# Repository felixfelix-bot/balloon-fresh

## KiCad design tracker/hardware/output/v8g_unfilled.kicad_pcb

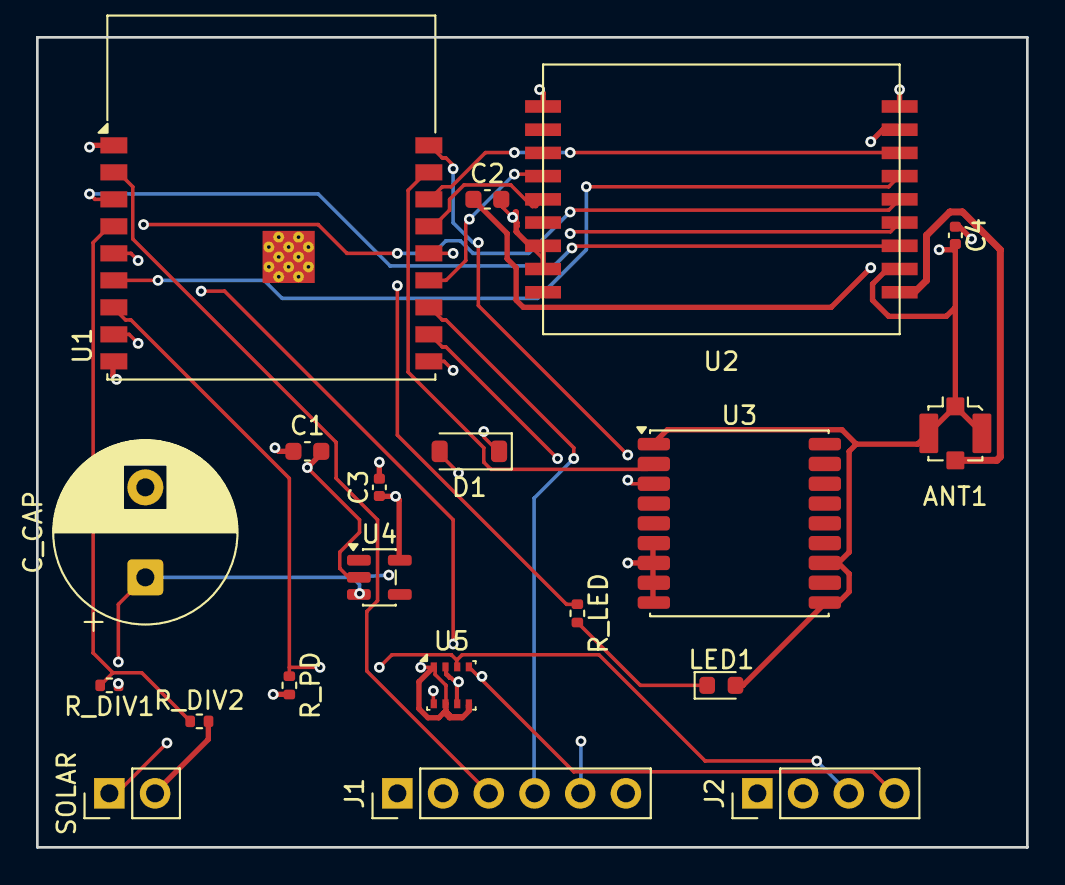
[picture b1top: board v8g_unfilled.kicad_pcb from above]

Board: 4 copper layers, 55.0 x 45.0 mm, 20 parts (0 on the bottom side), 22 nets.

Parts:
ANT1: U.FL; U.FL_Molex_MCRF_73412-0110_Vertical
C1, C2: 10uF; C_0603_1608Metric
C3, C4: 100nF; C_0402_1005Metric
C_CAP: 1F_5.5V; CP_Radial_D10.0mm_P5.00mm
D1: BAT54; D_SOD-123
J1: Prog_Header; PinHeader_1x06_P2.54mm_Vertical
J2: Debug_Header; PinHeader_1x04_P2.54mm_Vertical
LED1: LED_RED; LED_0603_1608Metric
R_DIV1, R_DIV2: 100k; R_0402_1005Metric
R_LED: 330R; R_0402_1005Metric
R_PD: 10k; R_0402_1005Metric
SOLAR: Solar_In; PinHeader_1x02_P2.54mm_Vertical
U1: ESP32-C3-WROOM-02
U2: LoRa2021_Gen4; LoRa2021_Castellated
U3: MAX-M10S; ublox_MAX
U4: TPS7A02; SOT-23-5
U5: BMP280; Bosch_LGA-8_2.5x2.5mm_P0.65mm_ClockwisePinNumbering

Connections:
+3V3: C1.1, C2.1, C3.1, C4.1, J1.2, J2.2, R_PD.2, U1.1, U2.1, U3.6, U3.7, U3.8, U3.9, U4.5, U5.2, U5.6, U5.8
EN: J1.3, U1.2
GND: ANT1.2, C1.2, C2.2, C3.2, C4.2, C_CAP.2, J1.1, J2.1, LED1.2, R_DIV2.2, SOLAR.2, U1.9, U1.19, U2.2, U2.8, U2.11, U2.12, U2.18, U3.1, U3.10, U3.12, U4.2, U5.1, U5.5, U5.7
GPS_RX: U1.17, U3.2
GPS_TX: U1.18, U3.3
I2C_SCL: J2.4, U1.8, U5.4
I2C_SDA: J2.3, R_PD.1, U1.7, U5.3
LED_A: LED1.1, R_LED.2
LED_DRIVE: R_LED.1, U1.14
LR_BUSY: U1.3, U2.7
LR_IRQ: U1.13, U2.15
LR_RST: U1.15, U2.14
RF_OUT: ANT1.1, U2.9
SOLAR_IN: D1.1, SOLAR.1
SPI_MISO: U1.16, U2.3
SPI_MOSI: U1.6, U2.4
SPI_NSS: U1.10, U2.6
SPI_SCK: U1.5, U2.5
UART0_RX: J1.5, U1.11
UART0_TX: J1.4, U1.12
VCAP: C_CAP.1, D1.2, R_DIV1.1, U4.1, U4.3
VDIV_MID: R_DIV1.2, R_DIV2.1, U1.4

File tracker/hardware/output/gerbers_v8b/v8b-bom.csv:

Comment,Designator,Footprint,Layer,Qty
U.FL,ANT1,U.FL_Molex_MCRF_73412-0110_Vertical,top,1
10uF,C1,C_0603_1608Metric,top,1
10uF,C2,C_0603_1608Metric,top,1
100nF,C3,C_0402_1005Metric,top,1
100nF,C4,C_0402_1005Metric,top,1
1F_5.5V,C_CAP,CP_Radial_D10.0mm_P5.00mm,top,1
BAT54,D1,D_SOD-123,top,1
Prog_Header,J1,PinHeader_1x06_P2.54mm_Vertical,top,1
Debug_Header,J2,PinHeader_1x04_P2.54mm_Vertical,top,1
LED_RED,LED1,LED_0603_1608Metric,top,1
100k,R_DIV1,R_0402_1005Metric,top,1
100k,R_DIV2,R_0402_1005Metric,top,1
330R,R_LED,R_0402_1005Metric,top,1
10k,R_PD,R_0402_1005Metric,top,1
Solar_In,SOLAR,PinHeader_1x02_P2.54mm_Vertical,top,1
ESP32-C3-WROOM-02,U1,ESP32-C3-WROOM-02,top,1
LR2021F33,U2,HOPERF_RFM9XW_SMD,top,1
MAX-M10S,U3,ublox_MAX,top,1
TPS7A02,U4,SOT-23-5,top,1
BMP280,U5,Bosch_LGA-8_2.5x2.5mm_P0.65mm_ClockwisePinNumbering,top,1

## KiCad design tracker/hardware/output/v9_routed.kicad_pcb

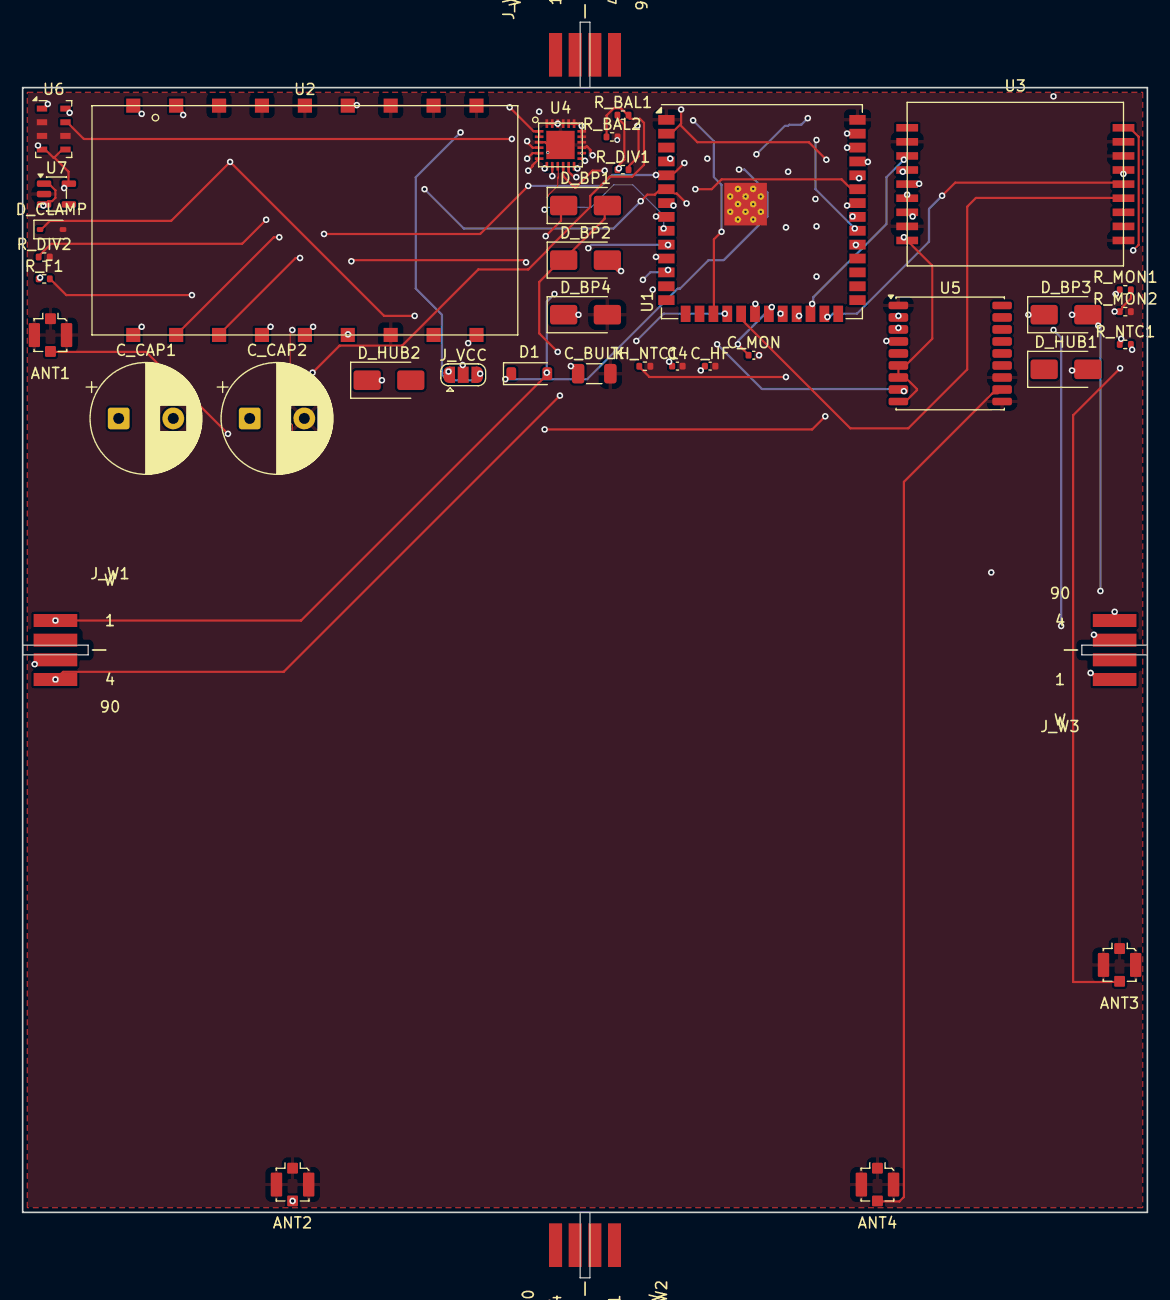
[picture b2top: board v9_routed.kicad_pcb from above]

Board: 4 copper layers, 103.0 x 103.0 mm, 39 parts (0 on the bottom side), 45 nets.

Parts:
ANT1: U.FL_433_TX; U.FL_Molex_MCRF_73412-0110_Vertical
ANT2: U.FL_2G4_RANGE; U.FL_Molex_MCRF_73412-0110_Vertical
ANT3: U.FL_2G4_RX; U.FL_Molex_MCRF_73412-0110_Vertical
ANT4: U.FL_GNSS_L1; U.FL_Molex_MCRF_73412-0110_Vertical
C4: 10uF; C_0402_1005Metric
C_BULK: 100uF; C_1206_3216Metric
C_CAP1, C_CAP2: 3.3F 2.7V (AVX SCC); CP_Radial_D10.0mm_P5.00mm
C_HF: 100nF; C_0402_1005Metric
C_MON: 10nF; C_0402_1005Metric
D1: BAT54; D_SOD-123
D_BP1, D_BP2, D_BP3, D_BP4: SS24; D_SMA
D_CLAMP: TVS clamp (set point TODO(unverified)); D_SOD-323
D_HUB1, D_HUB2: SS24; D_SMA
J_VCC: F33_VCC_SEL (5V raw | 3V3); SolderJumper-3_P1.3mm_Open_RoundedPad1.0x1.5mm
J_W1: WING_SOCKET_4P (hub wing interface 1); Wing_Tab_4P
J_W2: WING_SOCKET_4P (hub wing interface 2); Wing_Tab_4P
J_W3: WING_SOCKET_4P (hub wing interface 3); Wing_Tab_4P
J_W4: WING_SOCKET_4P (hub wing interface 4); Wing_Tab_4P
R_BAL1, R_BAL2: 10k; R_0402_1005Metric
R_DIV1, R_DIV2: 1M; R_0402_1005Metric
R_F1: 100R; R_0402_1005Metric
R_MON1, R_MON2: 4.7M; R_0402_1005Metric
R_NTC1: TODO(unverified) (sets ntc_r_ratio); R_0402_1005Metric
TH_NTC1: TODO(unverified) (NTC, R25/beta TODO); R_0402_1005Metric
U1: ESP32-S3-WROOM-1U-N8R8; ESP32-S3-WROOM-1U
U2: LoRa2021F33-2G4; LoRa2021F33_2G4
U3: LoRa2021_Castellated
U4: SX1280; SX1280_QFN24
U5: MAX-M10S; ublox_MAX
U6: MS5611-01BA; LGA-8_3x5mm_P1.25mm
U7: TPS7A02; SOT-23-5

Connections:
+3V3: J_VCC.3, R_F1.1, U1.2, U2.5, U3.1, U4.1, U4.2, U5.6, U5.7, U5.9, U6.1, U6.4, U6.5, U7.5
/ANT1_433_TX: ANT1.1, U2.9
/ANT2_2G4_RANGE: ANT2.1, U4.14
/ANT3_2G4_RX: ANT3.1, U3.10
/ANT4_GNSS_L1: ANT4.1, U5.11
/F33_BUSY: U1.12, U2.14
/F33_CS_N: U1.7, U2.13
/F33_IRQ: U1.17, U2.18
/F33_MISO: U1.6, U2.16, U3.3
/F33_MOSI: U1.5, U2.15, U3.4
/F33_RESET_N: U1.18, U2.17
/F33_SCK: U1.4, U2.12, U3.5
/F33_VCC: C_BULK.1, C_HF.1, D_CLAMP.1, J_VCC.2, R_MON1.1, U2.1
/F33_VSENSE: C_MON.1, R_MON1.2, R_MON2.1, U1.21
/GNSS_PPS: U1.23, U5.4
/GNSS_RX: U1.37, U5.3
/GNSS_TX: U1.36, U5.2
/GNSS_VCC: C4.1, R_F1.2, U5.8
/HUB_PV_MID1: D_HUB1.2, D_HUB2.1
/I2C_SCL: U1.38, U6.8
/I2C_SDA: U1.39, U6.7
/NTC_SENSE: R_NTC1.2, TH_NTC1.1
/SCAP_ADC: R_DIV1.2, R_DIV2.1
/SCAP_MID: C_CAP1.2, C_CAP2.1, R_BAL1.2, R_BAL2.1
/SX1280_ANT_SW: U1.35, U4.13
/SX1280_BUSY: U1.31, U4.5
/SX1280_CS_N: U1.10, U4.6
/SX1280_DIO1: U1.33, U4.10
/SX1280_DIO2: U1.11, U4.11
/SX1280_DIO3: U1.34, U4.12
/SX1280_MISO: U1.9, U4.9
/SX1280_MOSI: U1.8, U4.8
/SX1280_RESET_N: U1.32, U4.4
/SX1280_SCK: U1.22, U4.7
/U3_BUSY: U1.24, U3.7
/U3_CS_N: U1.20, U3.6
/U3_IRQ: U1.19, U3.15
/U3_RESET_N: U1.25, U3.14
/VSCAP: C_CAP1.1, D1.1, J_VCC.1, R_BAL1.1, R_DIV1.1, U7.1, U7.3
/VTCXO_VNTC: R_NTC1.1, U3.13
/W1_SOLAR_N: D_BP1.2, D_BP2.1, J_W1.4, J_W2.1
/W1_SOLAR_P: D1.2, D_BP1.1, J_W1.1
/W2_SOLAR_N: D_BP2.2, D_BP3.1, J_W2.4, J_W3.1
/W3_SOLAR_N: D_BP3.2, D_BP4.1, J_W3.4, J_W4.1
GND: ANT1.2, ANT2.2, ANT3.2, ANT4.2, C4.2, C_BULK.2, C_CAP2.2, C_HF.2, C_MON.2, D_BP4.2, D_CLAMP.2, J_W1.2, J_W2.2, J_W3.2, J_W4.2, J_W4.4, R_BAL2.2, R_DIV2.2, R_MON2.2, TH_NTC1.2, U1.1, U1.40, U1.41, U2.2, U2.3, U2.4, U2.6, U2.7, U2.8, U2.11, U3.2, U3.8, U3.11, U3.12, U3.18, U4.3, U4.15, U4.16, U4.17, U4.18, U4.19, U4.20, U4.21, U4.22, U4.23, U4.24, U4.25, U5.1, U5.10, U5.12, U6.2, U6.3, U6.6, U7.2

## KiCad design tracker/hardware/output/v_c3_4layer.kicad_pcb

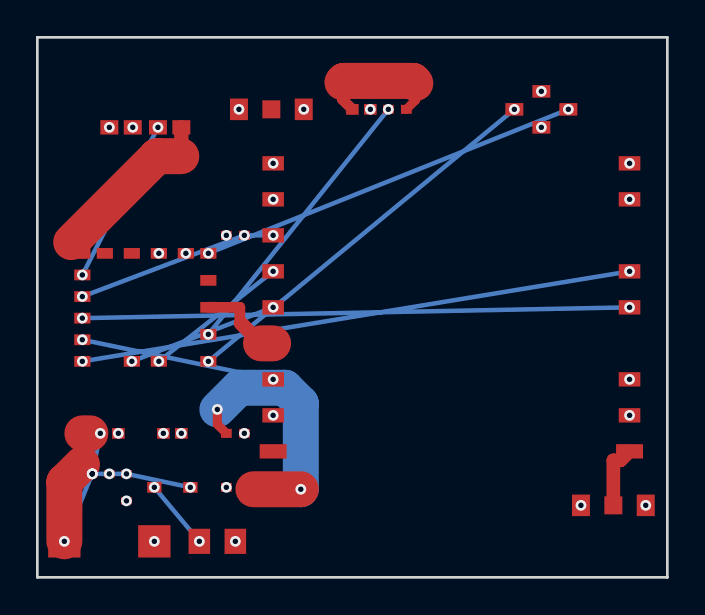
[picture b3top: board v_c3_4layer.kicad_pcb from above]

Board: 4 copper layers, 35.0 x 30.0 mm, 17 parts (0 on the bottom side), 20 nets.

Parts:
ANT1: U.FL-868
ANT2: U.FL-2400
C1, C2: 10uF
C_CAP: Supercap
D1: BAT54
FEM: SKY66112
LED1: LED-0603
R_DIV1, R_DIV2: 100k
R_LED: 1k
R_PD: 10k
SOLAR: Solar-Conn
U1: ESP32-C3
U2: LR2021F33
U3: MAX-M10S
U4: TPS7A02

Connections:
3V3: C2.1, FEM.VCC, R_DIV1.1, U1.VCC, U2.1, U3.1, U4.4
FEM_RX: FEM.RX, U1.GPIO8
FEM_TX: FEM.TX, U1.GPIO19
GND: ANT1.2, ANT1.3, ANT2.2, ANT2.3, C1.2, C2.2, C_CAP.2, FEM.GND, LED1.K, R_DIV2.2, R_PD.1, SOLAR.2, U1.GND, U2.2, U2.8, U2.10, U2.11, U2.16, U2.17, U3.2, U4.2
GPS_RX: U1.GPIO1, U3.3
GPS_TX: U1.GPIO0, U3.4
LED: R_LED.1, U1.GPIO18
LED_ANODE: LED1.A, R_LED.2
LR2021_BUSY: U1.GPIO4, U2.7
LR2021_DIO9: U1.GPIO5, U2.13
LR2021_RST: U1.GPIO3, U2.14
RF_2G4_2400: ANT2.1, U2.18
RF_SUB_868: ANT1.1, U2.9
SOLAR_IN: D1.A, SOLAR.1
SPI_MISO: R_PD.2, U1.GPIO2, U2.3
SPI_MOSI: U1.GPIO7, U2.4
SPI_NSS: U1.GPIO10, U2.6
SPI_SCK: U1.GPIO6, U2.5
VCAP: C1.1, C_CAP.1, D1.K, U4.1, U4.3
VDIV_MID: R_DIV1.2, R_DIV2.1
